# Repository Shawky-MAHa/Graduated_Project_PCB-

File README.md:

this PCB for a graduated project (ROV) in HTI

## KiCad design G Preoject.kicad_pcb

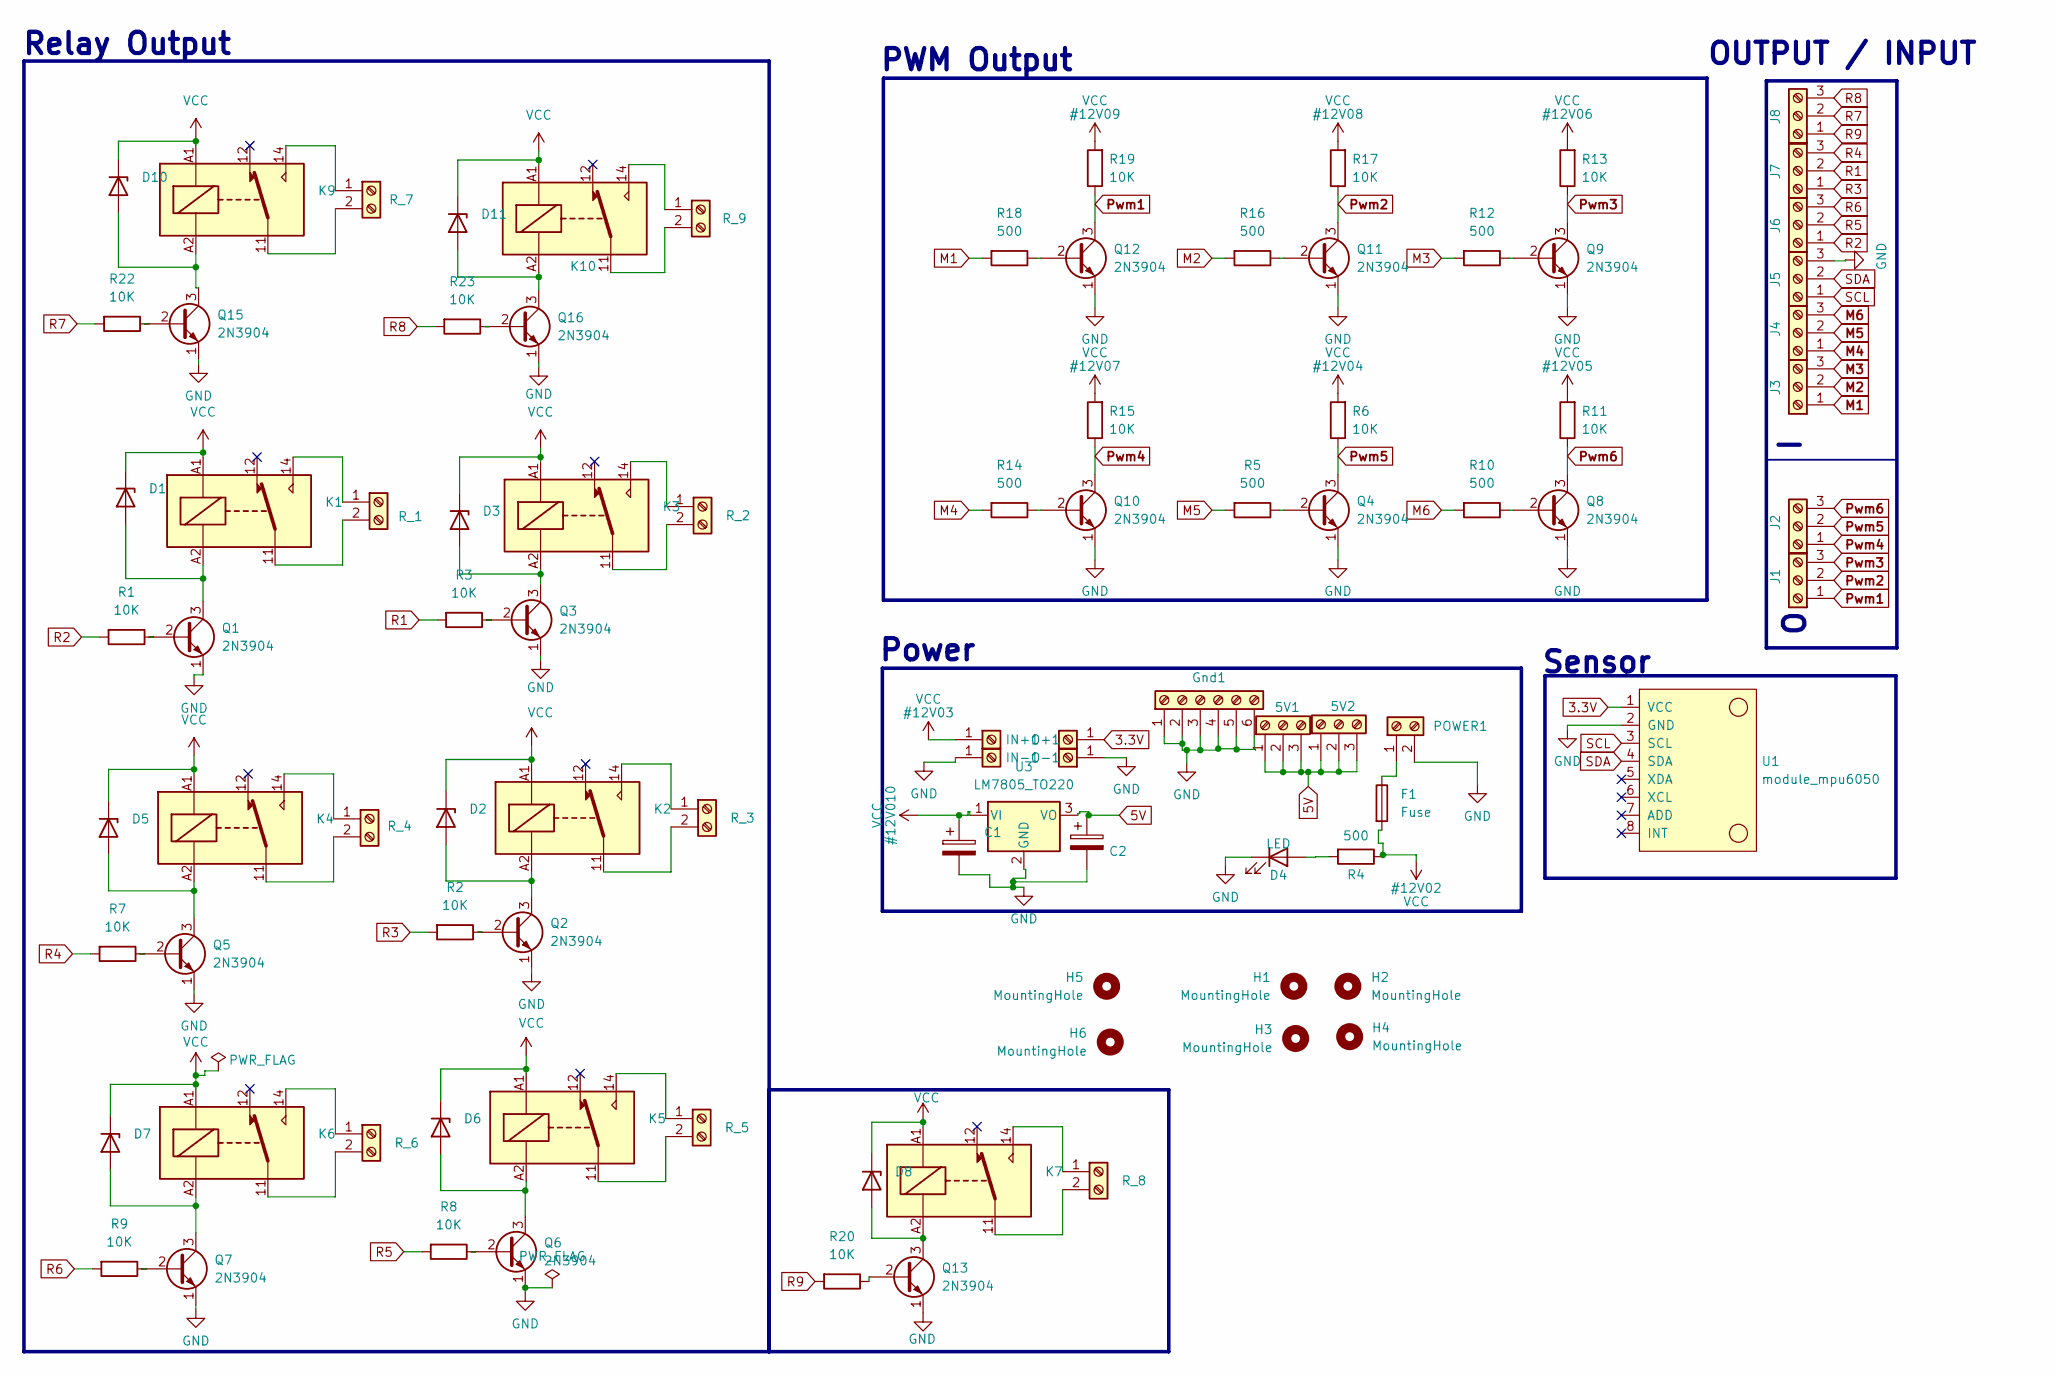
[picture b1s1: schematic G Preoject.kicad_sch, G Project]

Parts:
5V1, 5V2: Screw_Terminal_01x03; PinSocket_1x03_P2.54mm_Vertical
C1, C2: C_Polarized; CP_Radial_D5.0mm_P2.00mm
D1, D2, D3, D5, D6, D7, D8, D10, D11: 1N47xxA; D_DO-41_SOD81_P10.16mm_Horizontal
D4: LED; LED_D5.0mm
F1: Fuse; FUSE_4628
Gnd1: Screw_Terminal_01x03; PinSocket_1x06_P2.54mm_Vertical
H1, H2, H3, H4, H5, H6: MountingHole; MountingHole_3.2mm_M3
IN+1: Screw_Terminal_01x01; PinHeader_1x01_P2.54mm_Vertical
IN-1: Screw_Terminal_01x01; PinHeader_1x01_P2.54mm_Vertical
J1, J2, J3, J4, J5, J6, J7, J8: Screw_Terminal_01x03; TerminalBlock_Phoenix_MKDS-3-3-5.08_1x03_P5.08mm_Horizontal
K1, K2, K3, K4, K5, K6, K7, K9, K10: Relay_SPDT; Relay_SPDT_Finder_36.11
O+1: Screw_Terminal_01x01; PinHeader_1x01_P2.54mm_Vertical
O-1: Screw_Terminal_01x01; PinHeader_1x01_P2.54mm_Vertical
POWER1: Screw_Terminal_01x02; TerminalBlock_Altech_AK300-2_P5.00mm
Q1, Q2, Q3, Q4, Q5, Q6, Q7, Q8, Q9, Q10, Q11, Q12, Q13, Q15, Q16: 2N3904; TO-92_Inline
R1, R2, R3, R7, R8, R9, R20, R22, R23: 10K; R_Axial_DIN0411_L9.9mm_D3.6mm_P15.24mm_Horizontal
R4: 500; R_Axial_DIN0207_L6.3mm_D2.5mm_P15.24mm_Horizontal
R5, R10, R12, R14, R16, R18: 500; R_1206_3216Metric_Pad1.30x1.75mm_HandSolder
R6, R11, R13, R15, R17, R19: 10K; R_Axial_DIN0207_L6.3mm_D2.5mm_P10.16mm_Horizontal
R_1, R_2, R_3, R_4, R_5, R_6, R_7, R_8, R_9: Screw_Terminal_01x02; TerminalBlock_Phoenix_MKDS-1,5-2_1x02_P5.00mm_Horizontal
U1: module_mpu6050
U3: LM7805_TO220; TO-220-3_Vertical

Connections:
3.3V: O+1.1, U1.1 (VCC)
5V: 5V1.1, 5V1.2, 5V1.3, 5V2.1, 5V2.2, 5V2.3, C2.1, U3.3 (VO)
GND: C1.2, C2.2, D4.1 (K), Gnd1.1, Gnd1.2, Gnd1.3, Gnd1.4, Gnd1.5, Gnd1.6, IN-1.1, J5.3, O-1.1, POWER1.2, Q1.1 (E), Q2.1 (E), Q3.1 (E), Q4.1 (E), Q5.1 (E), Q6.1 (E), Q7.1 (E), Q8.1 (E), Q9.1 (E), Q10.1 (E), Q11.1 (E), Q12.1 (E), Q13.1 (E), Q15.1 (E), Q16.1 (E), U1.2 (GND), U3.2 (GND)
M1: J3.1, R18.2
M2: J3.2, R16.2
M3: J3.3, R12.2
M4: J4.1, R14.2
M5: J4.2, R5.2
M6: J4.3, R10.2
unnamed: D1.2 (A), K1.A2, Q1.3 (C)
unnamed: D2.2 (A), K2.A2, Q2.3 (C)
unnamed: D3.2 (A), K3.A2, Q3.3 (C)
unnamed: D4.2 (A), R4.2
unnamed: D5.2 (A), K4.A2, Q5.3 (C)
unnamed: D6.2 (A), K5.A2, Q6.3 (C)
unnamed: D7.2 (A), K6.A2, Q7.3 (C)
unnamed: D8.2 (A), K7.A2, Q13.3 (C)
unnamed: D10.2 (A), K9.A2, Q15.3 (C)
unnamed: D11.2 (A), K10.A2, Q16.3 (C)
unnamed: F1.1, POWER1.1
unnamed: Q1.2 (B), R1.1
unnamed: Q2.2 (B), R2.1
unnamed: Q3.2 (B), R3.1
unnamed: Q4.2 (B), R5.1
unnamed: Q5.2 (B), R7.1
unnamed: Q6.2 (B), R8.1
unnamed: Q7.2 (B), R9.1
unnamed: Q8.2 (B), R10.1
unnamed: Q9.2 (B), R12.1
unnamed: Q10.2 (B), R14.1
unnamed: Q11.2 (B), R16.1
unnamed: Q12.2 (B), R18.1
unnamed: Q13.2 (B), R20.1
unnamed: Q15.2 (B), R22.1
unnamed: Q16.2 (B), R23.1
unnamed: K1.14, R_1.1
unnamed: K1.11, R_1.2
unnamed: K3.14, R_2.1
unnamed: K3.11, R_2.2
unnamed: K2.14, R_3.1
unnamed: K2.11, R_3.2
unnamed: K4.14, R_4.1
unnamed: K4.11, R_4.2
unnamed: K5.14, R_5.1
unnamed: K5.11, R_5.2
unnamed: K6.14, R_6.1
unnamed: K6.11, R_6.2
unnamed: K9.14, R_7.1
unnamed: K9.11, R_7.2
unnamed: K7.14, R_8.1
unnamed: K7.11, R_8.2
unnamed: K10.14, R_9.1
unnamed: K10.11, R_9.2
Pwm1: J1.1, Q12.3 (C), R19.1
Pwm2: J1.2, Q11.3 (C), R17.1
Pwm3: J1.3, Q9.3 (C), R13.1
Pwm4: J2.1, Q10.3 (C), R15.1
Pwm5: J2.2, Q4.3 (C), R6.1
Pwm6: J2.3, Q8.3 (C), R11.1
R1: J7.2, R3.2
R2: J6.1, R1.2
R3: J7.1, R2.2
R4: J7.3, R7.2
R5: J6.2, R8.2
R6: J6.3, R9.2
R7: J8.2, R22.2
R8: J8.3, R23.2
R9: J8.1, R20.2
SCL: J5.1, U1.3 (SCL)
SDA: J5.2, U1.4 (SDA)
VCC: C1.1, D1.1 (K), D2.1 (K), D3.1 (K), D5.1 (K), D6.1 (K), D7.1 (K), D8.1 (K), D10.1 (K), D11.1 (K), F1.2, IN+1.1, K1.A1, K2.A1, K3.A1, K4.A1, K5.A1, K6.A1, K7.A1, K9.A1, K10.A1, R4.1, R6.2, R11.2, R13.2, R15.2, R17.2, R19.2, U3.1 (VI)

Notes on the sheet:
Sensor
OUTPUT / INPUT
Power
PWM Output
Relay Output

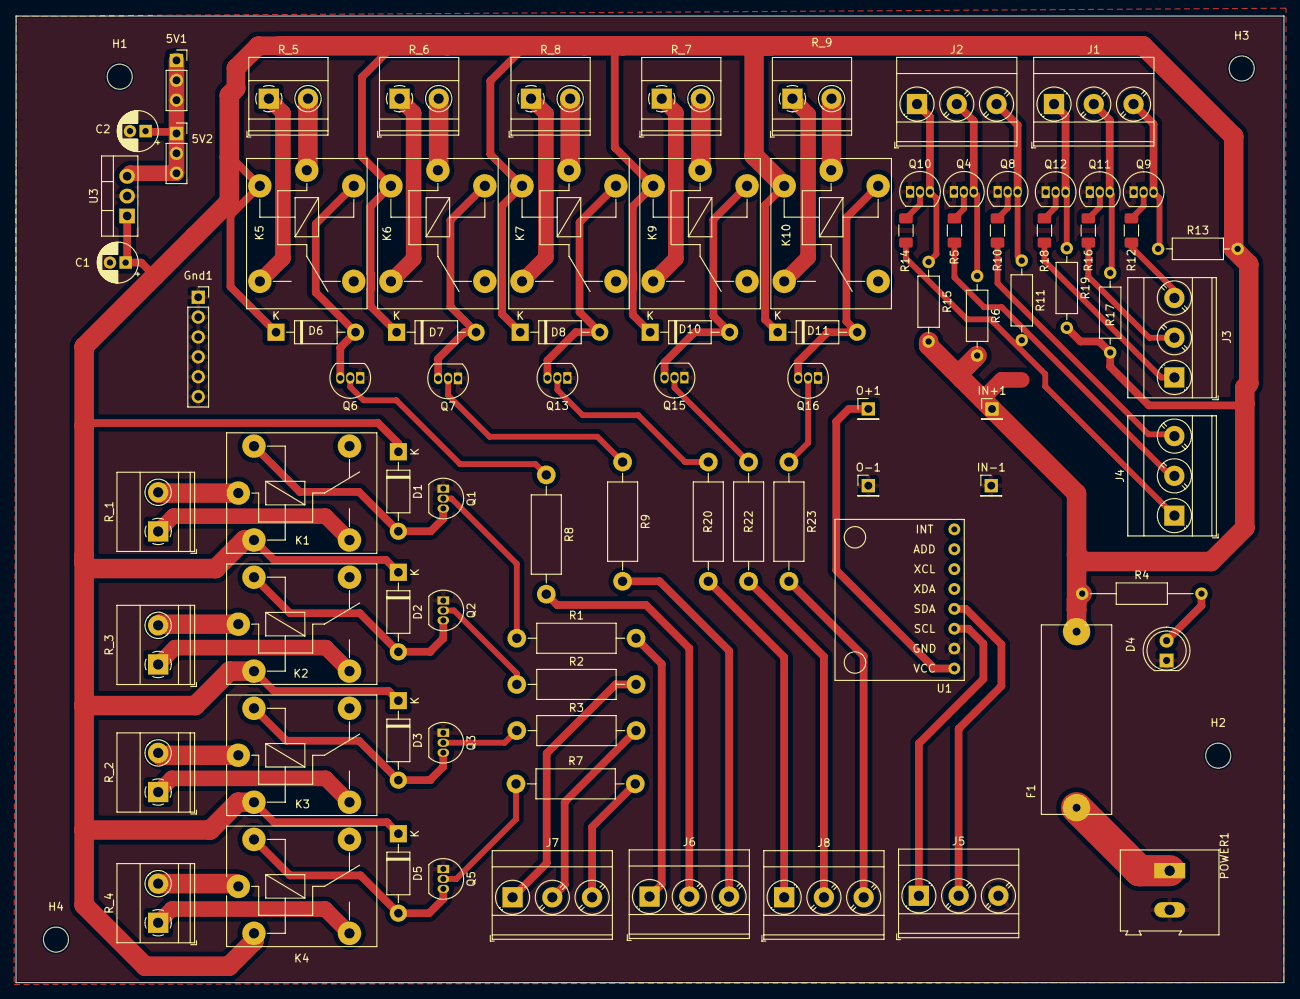
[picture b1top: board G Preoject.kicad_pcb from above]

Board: 2 copper layers, 162.0 x 123.5 mm, 90 parts (0 on the bottom side), 71 nets.

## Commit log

2024-05-13 graduated project
